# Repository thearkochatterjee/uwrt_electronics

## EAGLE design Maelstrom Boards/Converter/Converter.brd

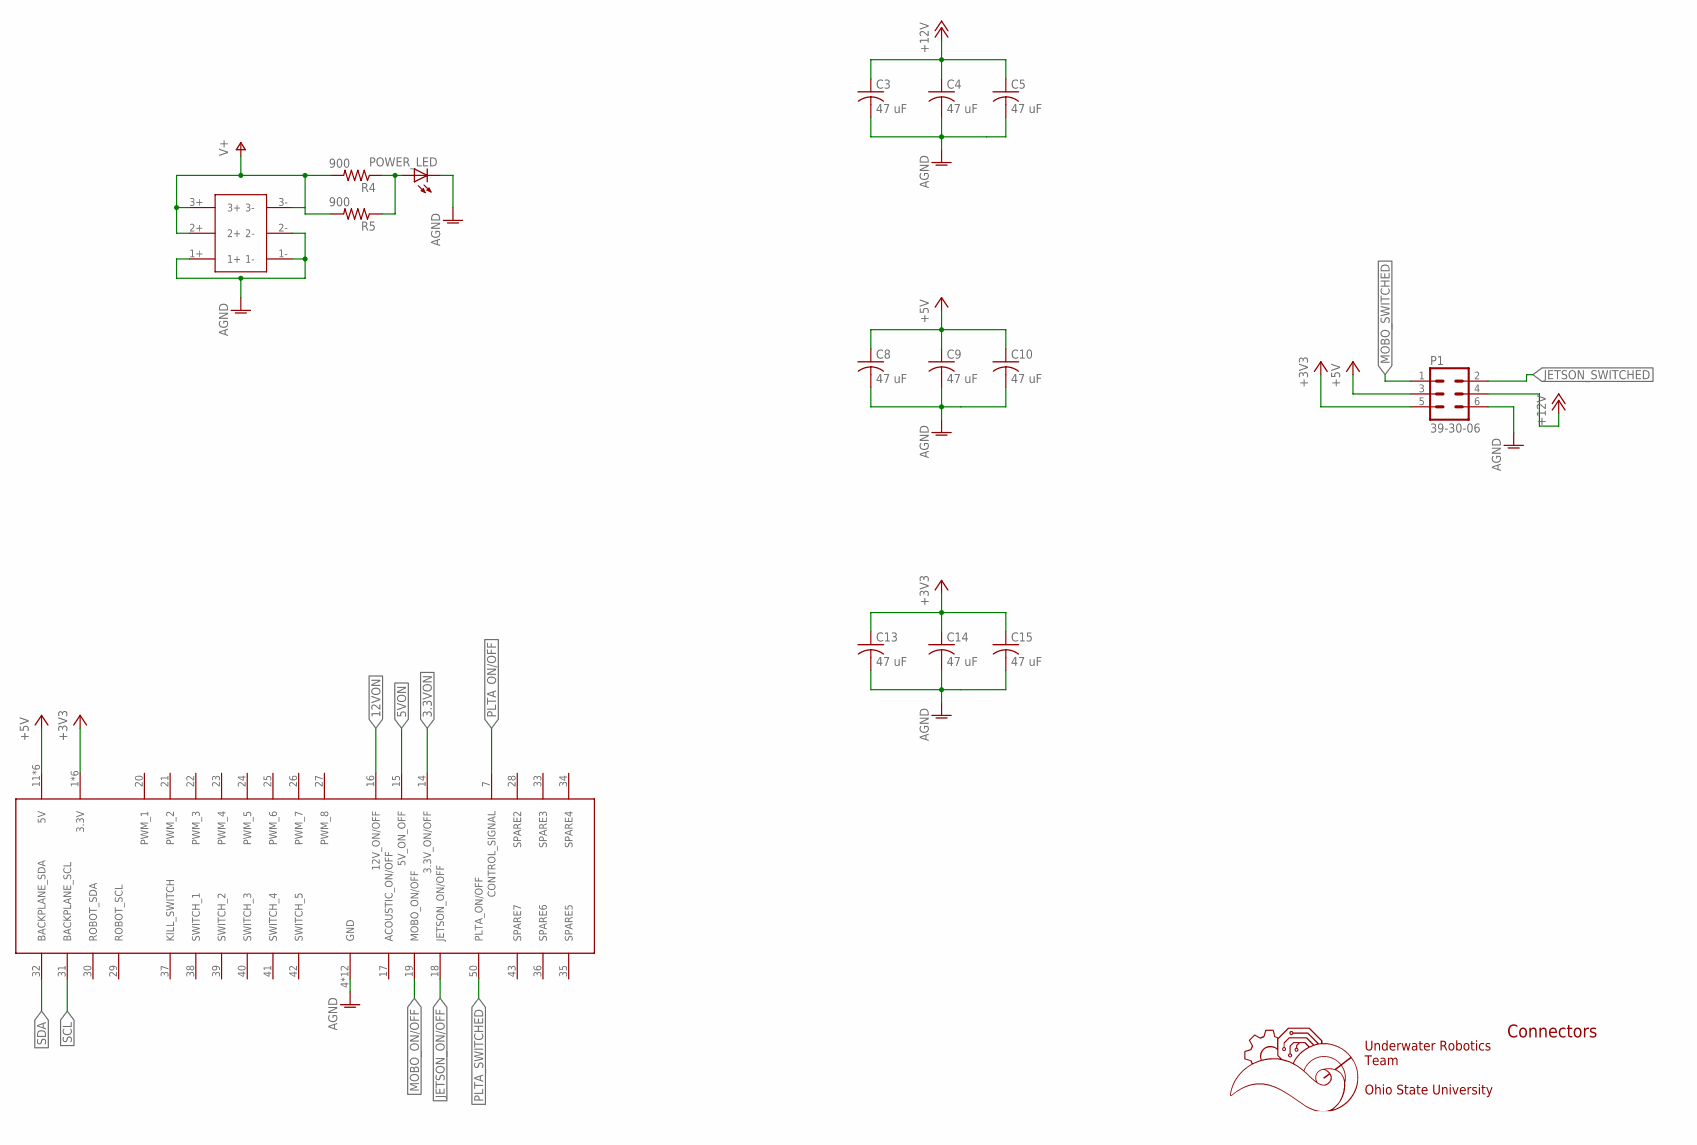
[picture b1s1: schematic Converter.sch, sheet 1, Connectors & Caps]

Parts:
C3, C4, C5, C8, C9, C10, C13, C14, C15: 47 uF; C1206K
P1: 39-30-06; 39-30-?06?
POWER_LED: LEDCHIPLED_0603; CHIPLED_0603
R4, R5: 900; R0603
U$1: 5530843-EDGE; 5530843-6-BOARDFINGERS
U$3: 6PIN-VERT; 6PIN_VERT

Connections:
3.3VON: U$1.14 (3.3V_ON/OFF); also elsewhere on the board
5VON: U$1.15 (5V_ON_OFF); also elsewhere on the board
12VON: U$1.16 (12V_ON/OFF); also elsewhere on the board
+3V3: C13.1, C14.1, C15.1, P1.5, U$1.1 (3.3V), U$1.2 (3.3V), U$1.3 (3.3V), U$1.54 (3.3V), U$1.55 (3.3V), U$1.56 (3.3V); also elsewhere on the board
+5V: C8.1, C9.1, C10.1, P1.3, U$1.11 (5V), U$1.12 (5V), U$1.13 (5V), U$1.44 (5V), U$1.45 (5V), U$1.46 (5V); also elsewhere on the board
+12V: C3.1, C4.1, C5.1, P1.4; also elsewhere on the board
AGND: C3.2, C4.2, C5.2, C8.2, C9.2, C10.2, C13.2, C14.2, C15.2, P1.6, POWER_LED.C, U$1.4 (GND), U$1.5 (GND), U$1.6 (GND), U$1.8 (GND), U$1.9 (GND), U$1.10 (GND), U$1.47 (GND), U$1.48 (GND), U$1.49 (GND), U$1.51 (GND), U$1.52 (GND), U$1.53 (GND), U$3.1+, U$3.1-, U$3.2-; also elsewhere on the board
JETSON_ON/OFF: U$1.18 (JETSON_ON/OFF); also elsewhere on the board
JETSON_SWITCHED: P1.2; also elsewhere on the board
MOBO_ON/OFF: U$1.19 (MOBO_ON/OFF); also elsewhere on the board
MOBO_SWITCHED: P1.1; also elsewhere on the board
unnamed: POWER_LED.A, R4.1, R5.1
PLTA_ON/OFF: U$1.7 (CONTROL_SIGNAL); also elsewhere on the board
PLTA_SWITCHED: U$1.50 (PLTA_ON/OFF); also elsewhere on the board
SCL: U$1.31 (BACKPLANE_SCL); also elsewhere on the board
SDA: U$1.32 (BACKPLANE_SDA); also elsewhere on the board
V+: R4.2, R5.2, U$3.2+, U$3.3+, U$3.3-; also elsewhere on the board

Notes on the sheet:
Underwater Robotics Team Ohio State University
Connectors

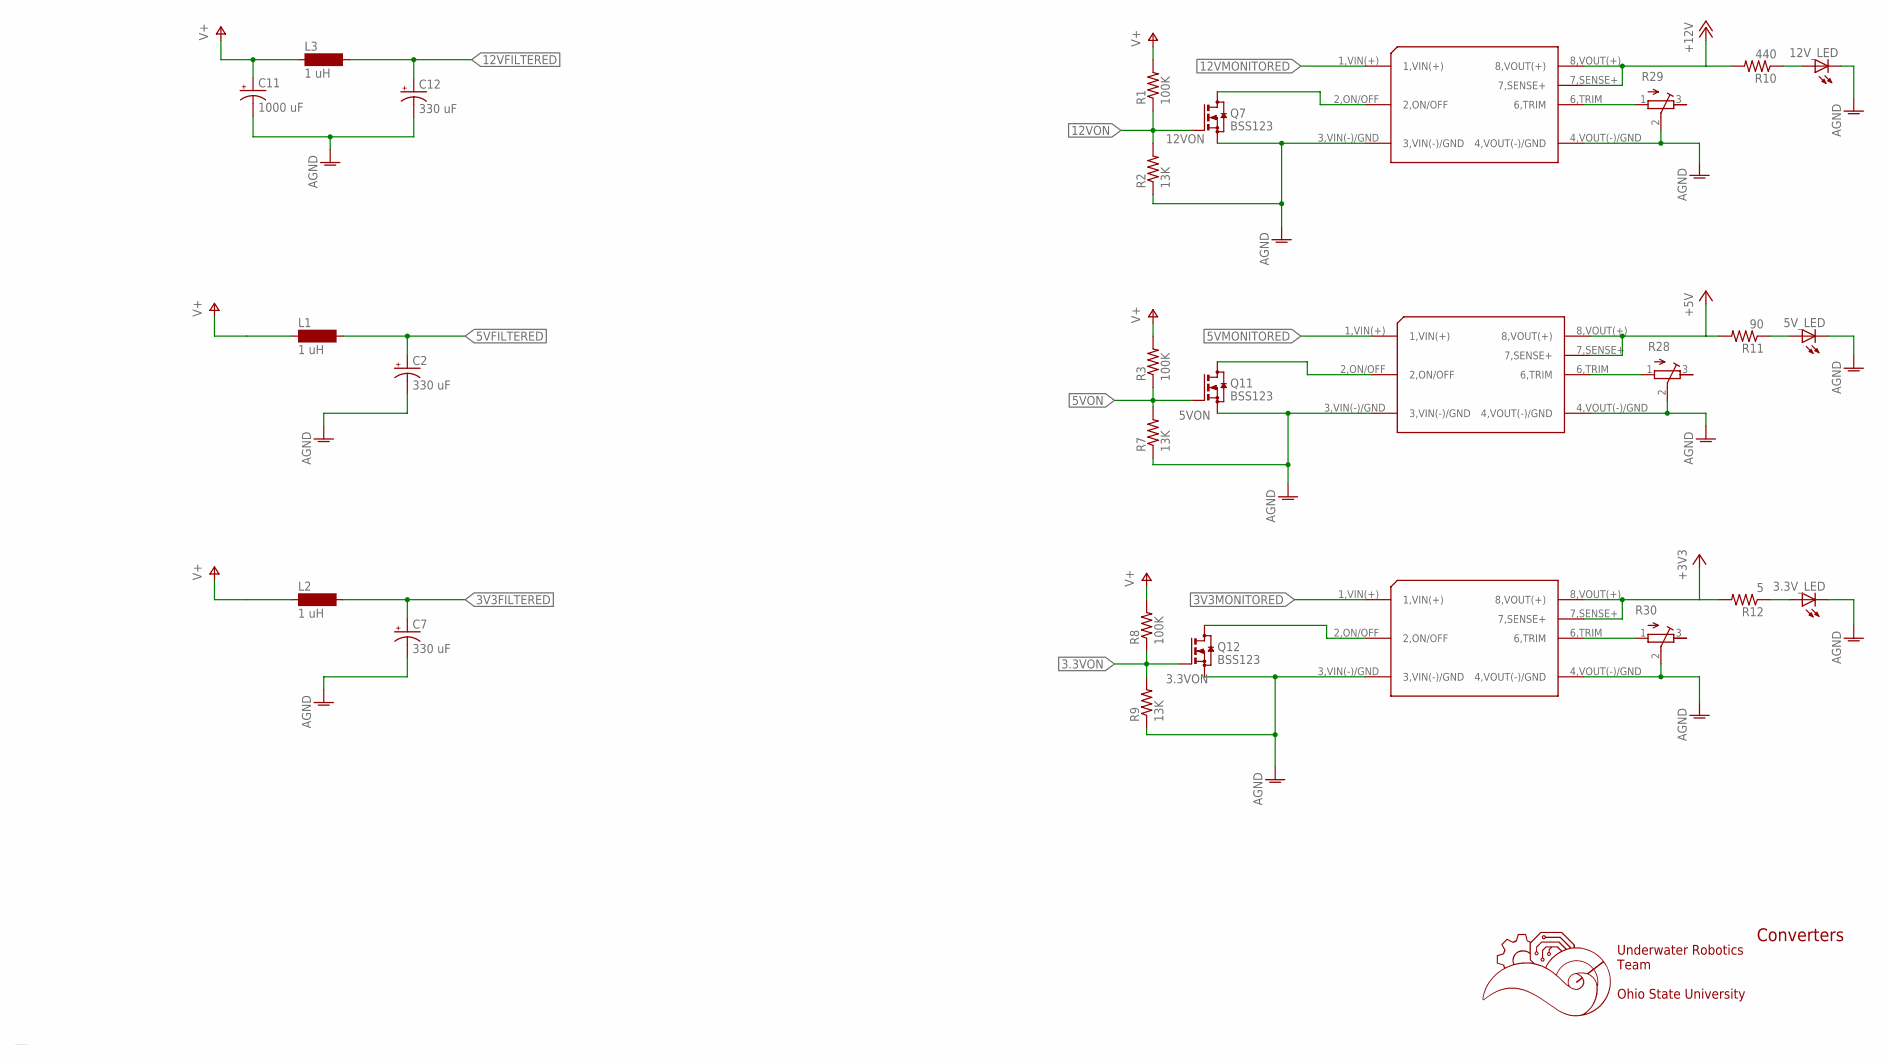
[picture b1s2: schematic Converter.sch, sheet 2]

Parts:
3.3VCONVERTER, 5VCONVERTER, 12VCONVERTER: CONVERTER
3.3V_LED, 5V_LED, 12V_LED: LEDCHIPLED_0603; CHIPLED_0603
C2, C7, C12: 330 uF; E5-10,5
C11: 1000 uF; E5-13
L1, L2, L3: 1 uH; MS85
Q7, Q11, Q12: BSS123; SOT23
R1, R3, R8: 100K; R0603
R2, R7, R9: 13K; R0603
R10: 440; R0603
R11: 90; R0603
R12: 5; R0603
R28, R29, R30: R-TRIMM3103; RTRIM3103

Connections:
3.3VON: Q12.1 (G), R8.1, R9.2; also elsewhere on the board
3V3FILTERED: C7.+, L2.2; also elsewhere on the board
3V3MONITORED: 3.3VCONVERTER.1,VIN(+); also elsewhere on the board
5VFILTERED: C2.+, L1.2; also elsewhere on the board
5VMONITORED: 5VCONVERTER.1,VIN(+); also elsewhere on the board
5VON: Q11.1 (G), R3.1, R7.2; also elsewhere on the board
12VFILTERED: C12.+, L3.2; also elsewhere on the board
12VMONITORED: 12VCONVERTER.1,VIN(+); also elsewhere on the board
12VON: Q7.1 (G), R1.1, R2.2; also elsewhere on the board
+3V3: 3.3VCONVERTER.7,SENSE+, 3.3VCONVERTER.8,VOUT(+), R12.2; also elsewhere on the board
+5V: 5VCONVERTER.7,SENSE+, 5VCONVERTER.8,VOUT(+), R11.2; also elsewhere on the board
+12V: 12VCONVERTER.7,SENSE+, 12VCONVERTER.8,VOUT(+), R10.2; also elsewhere on the board
AGND: 3.3VCONVERTER.3,VIN(-)/GND, 3.3VCONVERTER.4,VOUT(-)/GND, 3.3V_LED.C, 5VCONVERTER.3,VIN(-)/GND, 5VCONVERTER.4,VOUT(-)/GND, 5V_LED.C, 12VCONVERTER.3,VIN(-)/GND, 12VCONVERTER.4,VOUT(-)/GND, 12V_LED.C, C2.-, C7.-, C11.-, C12.-, Q7.2 (S), Q11.2 (S), Q12.2 (S), R2.1, R7.1, R9.1, R28.2 (S), R29.2 (S), R30.2 (S); also elsewhere on the board
unnamed: 12VCONVERTER.6,TRIM, R29.1 (A)
unnamed: 5VCONVERTER.6,TRIM, R28.1 (A)
unnamed: 3.3VCONVERTER.6,TRIM, R30.1 (A)
unnamed: 3.3VCONVERTER.2,ON/OFF, Q12.3 (D)
unnamed: 12V_LED.A, R10.1
unnamed: 5V_LED.A, R11.1
unnamed: 3.3V_LED.A, R12.1
unnamed: 12VCONVERTER.2,ON/OFF, Q7.3 (D)
unnamed: 5VCONVERTER.2,ON/OFF, Q11.3 (D)
V+: C11.+, L1.1, L2.1, L3.1, R1.2, R3.2, R8.2; also elsewhere on the board

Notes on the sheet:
C:/Users/blain/Downloads/Black and White.bmp
Underwater Robotics Team Ohio State University
Converters

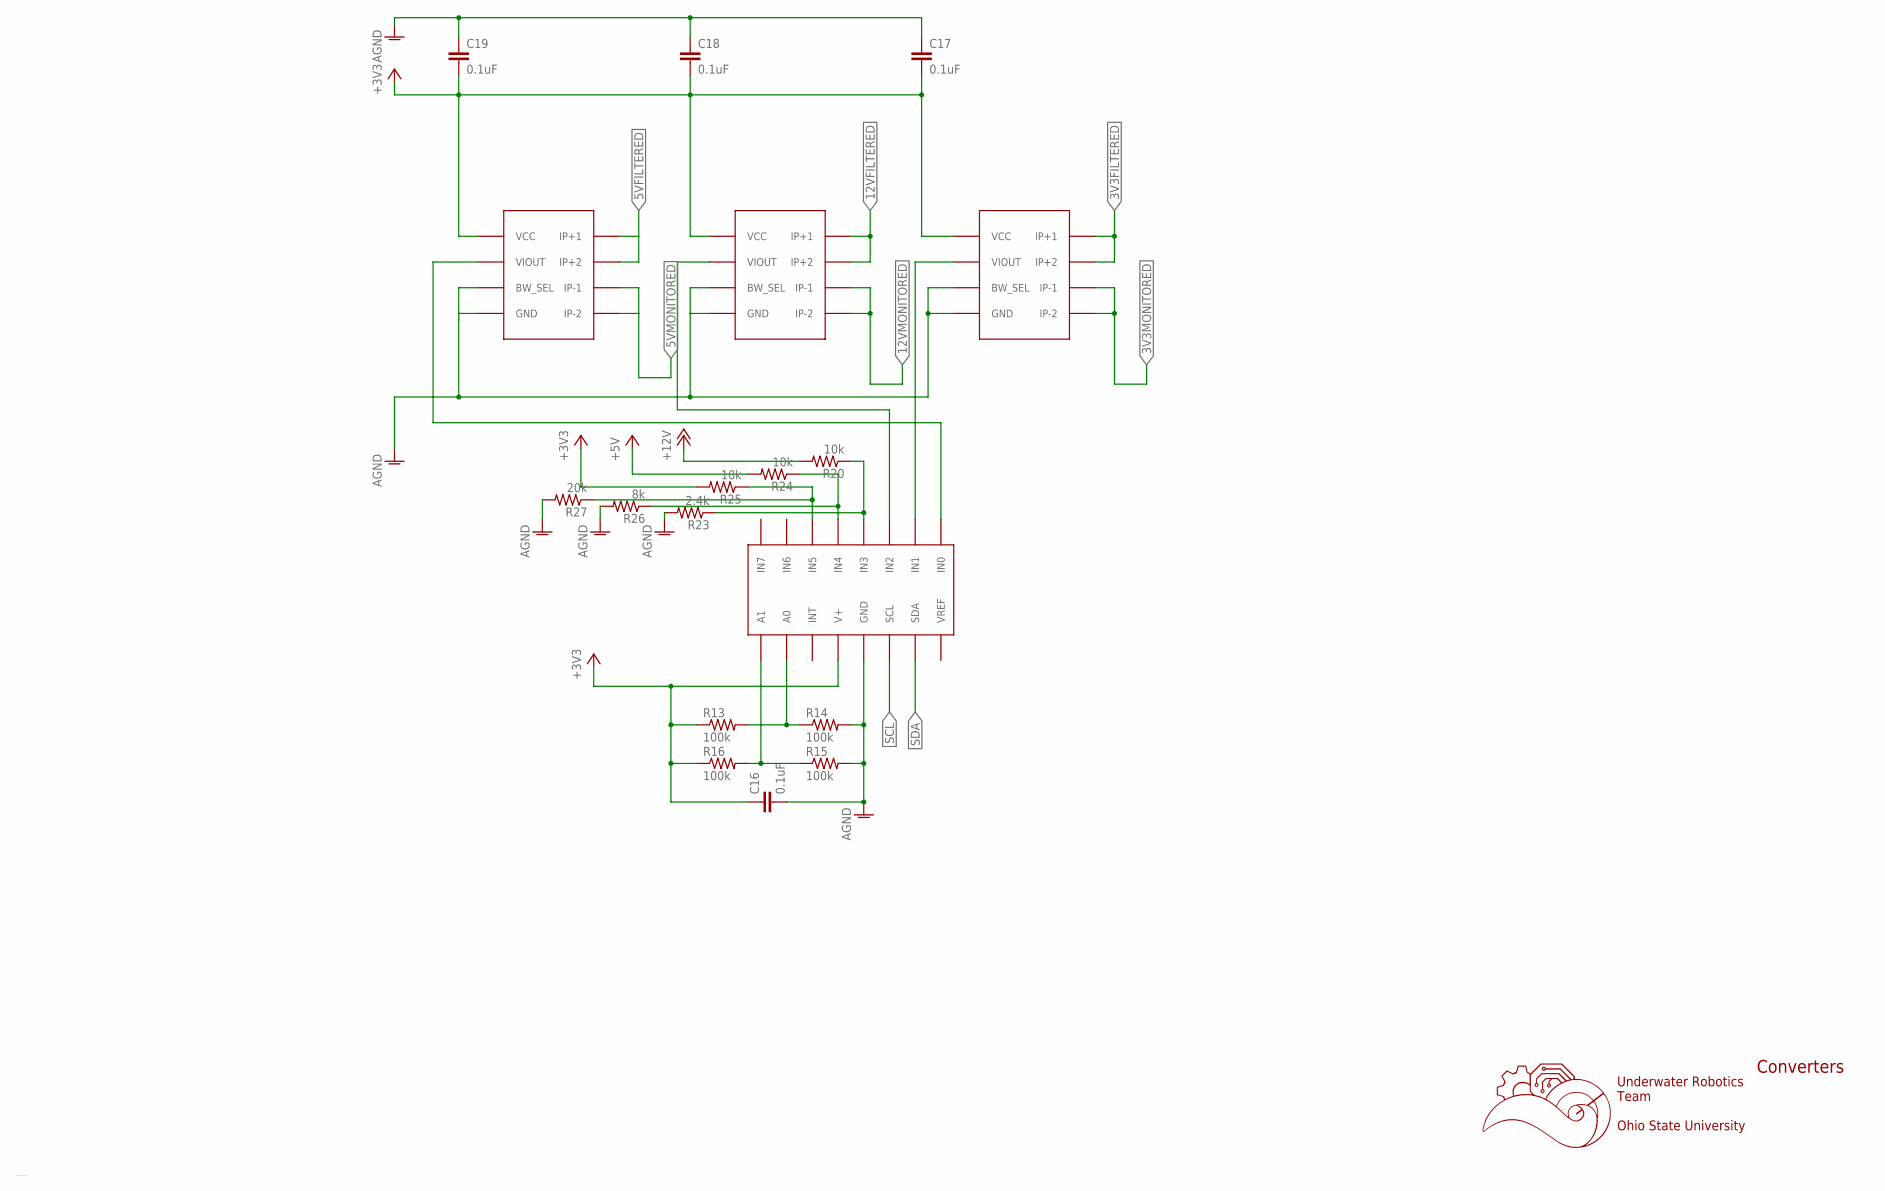
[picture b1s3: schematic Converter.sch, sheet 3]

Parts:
1C, 1C1, 1C2: ACS722; SOIC-8
C16, C17, C18, C19: 0.1uF; C0603
R13, R14, R15, R16: 100k; R0603
R20, R24, R25: 10k; R0603
R23: 2.4k; R0603
R26: 8k; R0603
R27: 20k; R0603
U$2: ADC128D818; TSSOP-16

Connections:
3V3FILTERED: 1C2.IP+1, 1C2.IP+2; also elsewhere on the board
3V3MONITORED: 1C2.IP-1, 1C2.IP-2; also elsewhere on the board
5VFILTERED: 1C.IP+1, 1C.IP+2; also elsewhere on the board
5VMONITORED: 1C.IP-1, 1C.IP-2; also elsewhere on the board
12VFILTERED: 1C1.IP+1, 1C1.IP+2; also elsewhere on the board
12VMONITORED: 1C1.IP-1, 1C1.IP-2; also elsewhere on the board
+3V3: 1C.VCC, 1C1.VCC, 1C2.VCC, C16.1, C17.2, C18.2, C19.2, R13.1, R16.1, R25.2, U$2.V+; also elsewhere on the board
+5V: R24.2; also elsewhere on the board
+12V: R20.2; also elsewhere on the board
AGND: 1C.BW_SEL, 1C.GND, 1C1.BW_SEL, 1C1.GND, 1C2.BW_SEL, 1C2.GND, C16.2, C17.1, C18.1, C19.1, R14.2, R15.2, R23.2, R26.2, R27.2, U$2.GND; also elsewhere on the board
unnamed: 1C.VIOUT, U$2.IN0
unnamed: 1C1.VIOUT, U$2.IN2
unnamed: 1C2.VIOUT, U$2.IN1
unnamed: R24.1, R26.1, U$2.IN4
unnamed: R25.1, R27.1, U$2.IN5
unnamed: R20.1, R23.1, U$2.IN3
unnamed: R13.2, R14.1, U$2.A0
unnamed: R15.1, R16.2, U$2.A1
SCL: U$2.SCL; also elsewhere on the board
SDA: U$2.SDA; also elsewhere on the board

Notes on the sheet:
C:/Users/blain/Downloads/Black and White.bmp
Underwater Robotics Team Ohio State University
Converters

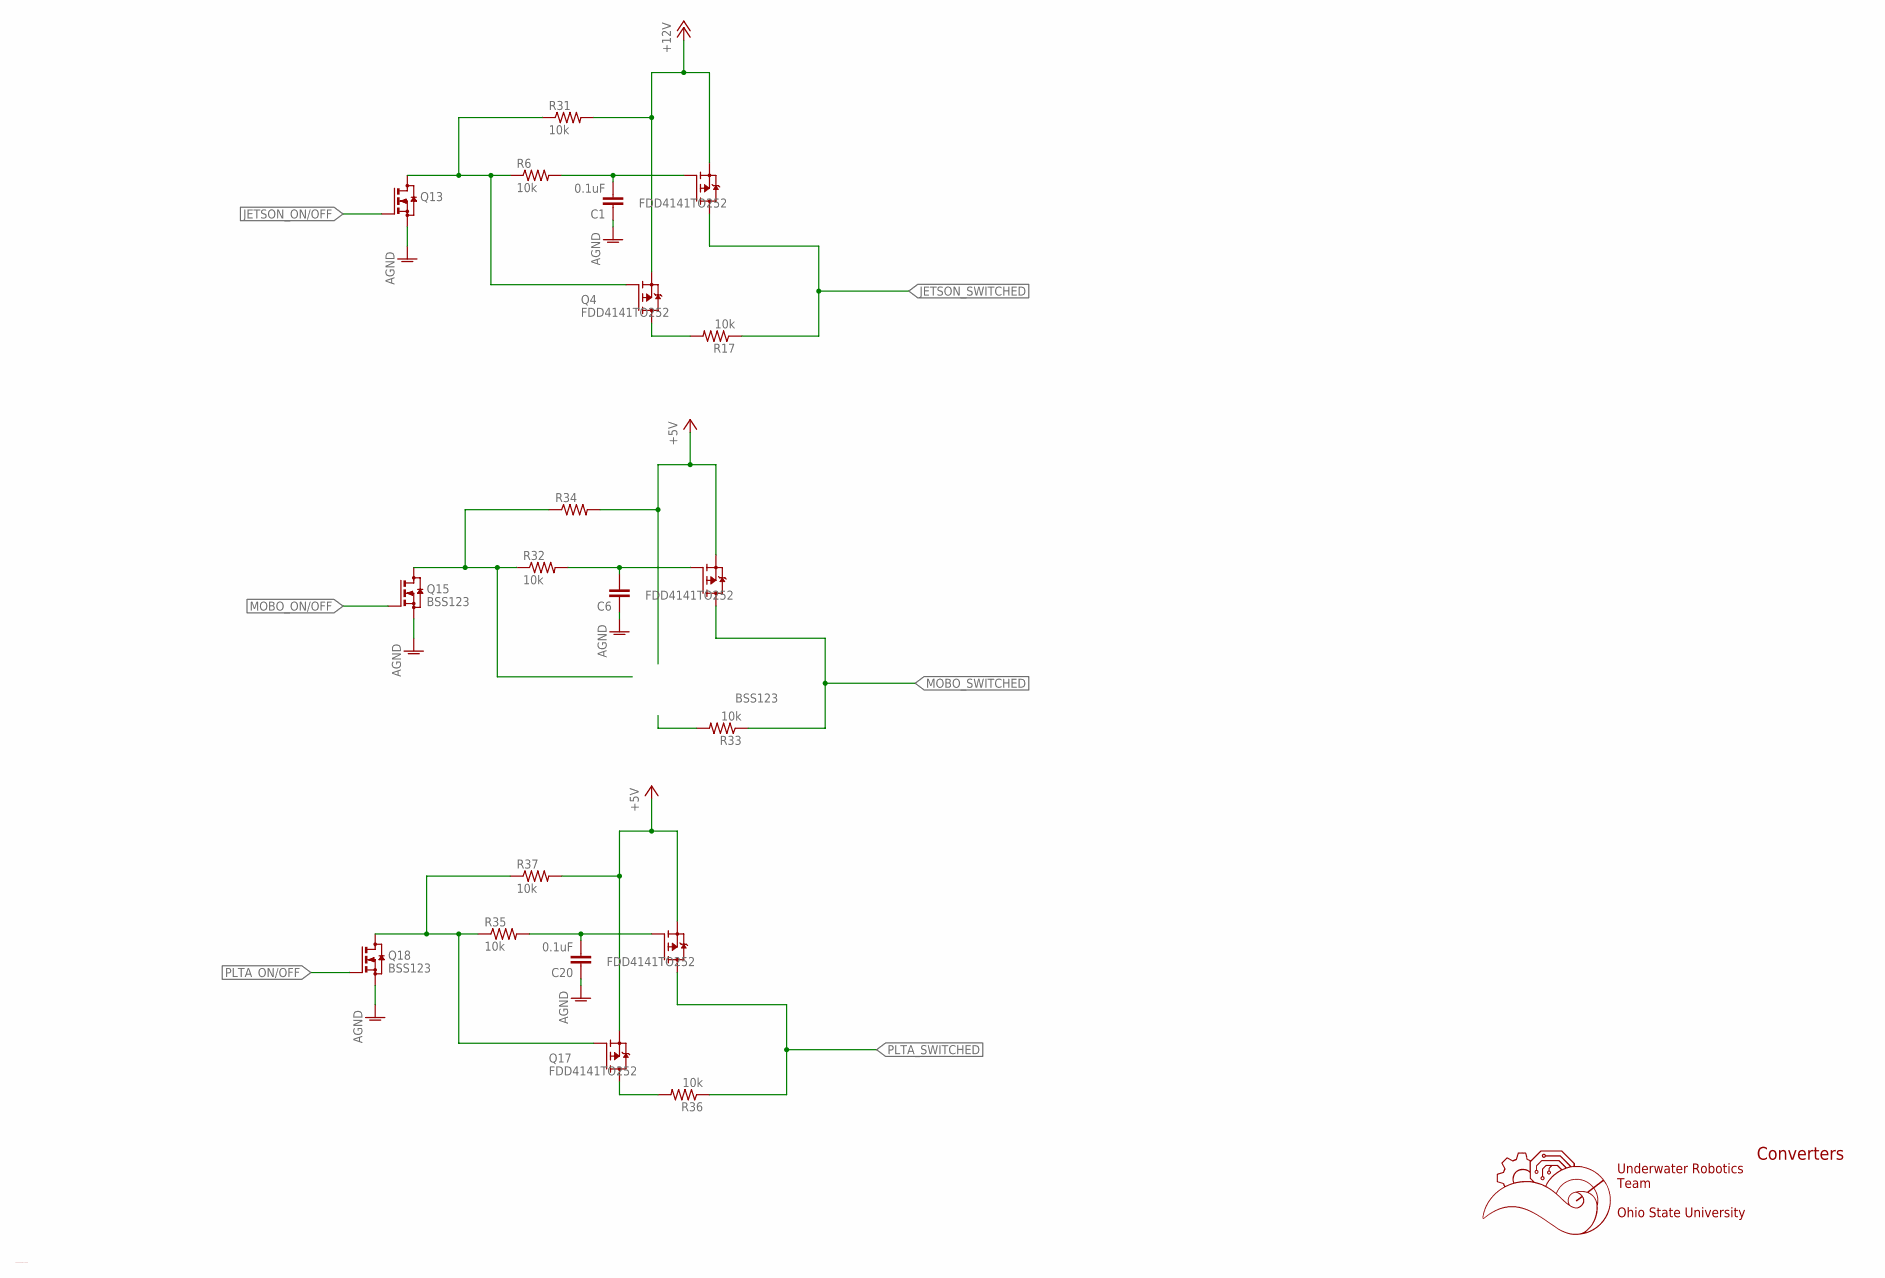
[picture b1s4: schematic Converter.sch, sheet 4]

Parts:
C1, C6, C20: 0.1uF; C0603
Q1, Q4, Q5, Q16, Q17: FDD4141TO252; TO252
Q13, Q15, Q18: BSS123; SOT23
R6, R17, R31, R32, R33, R34, R35, R36, R37: 10k; R0603

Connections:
+5V: Q5.2 (S), Q16.2 (S), Q17.2 (S), R34.2, R37.2; also elsewhere on the board
+12V: Q1.2 (S), Q4.2 (S), R31.2; also elsewhere on the board
AGND: C1.1, C6.1, C20.1, Q13.2 (S), Q15.2 (S), Q18.2 (S); also elsewhere on the board
JETSON_ON/OFF: Q13.1 (G); also elsewhere on the board
JETSON_SWITCHED: Q1.3 (D), R17.1; also elsewhere on the board
MOBO_ON/OFF: Q15.1 (G); also elsewhere on the board
MOBO_SWITCHED: Q5.3 (D), R33.1; also elsewhere on the board
unnamed: Q4.1 (G), Q13.3 (D), R6.1, R31.1
unnamed: Q4.3 (D), R17.2
unnamed: C1.2, Q1.1 (G), R6.2
unnamed: Q15.3 (D), R32.1, R34.1
unnamed: C6.2, Q5.1 (G), R32.2
unnamed: Q17.1 (G), Q18.3 (D), R35.1, R37.1
unnamed: C20.2, Q16.1 (G), R35.2
unnamed: Q17.3 (D), R36.2
PLTA_ON/OFF: Q18.1 (G); also elsewhere on the board
PLTA_SWITCHED: Q16.3 (D), R36.1; also elsewhere on the board

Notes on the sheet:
C:/Users/blain/Downloads/Black and White.bmp
Underwater Robotics Team Ohio State University
Converters

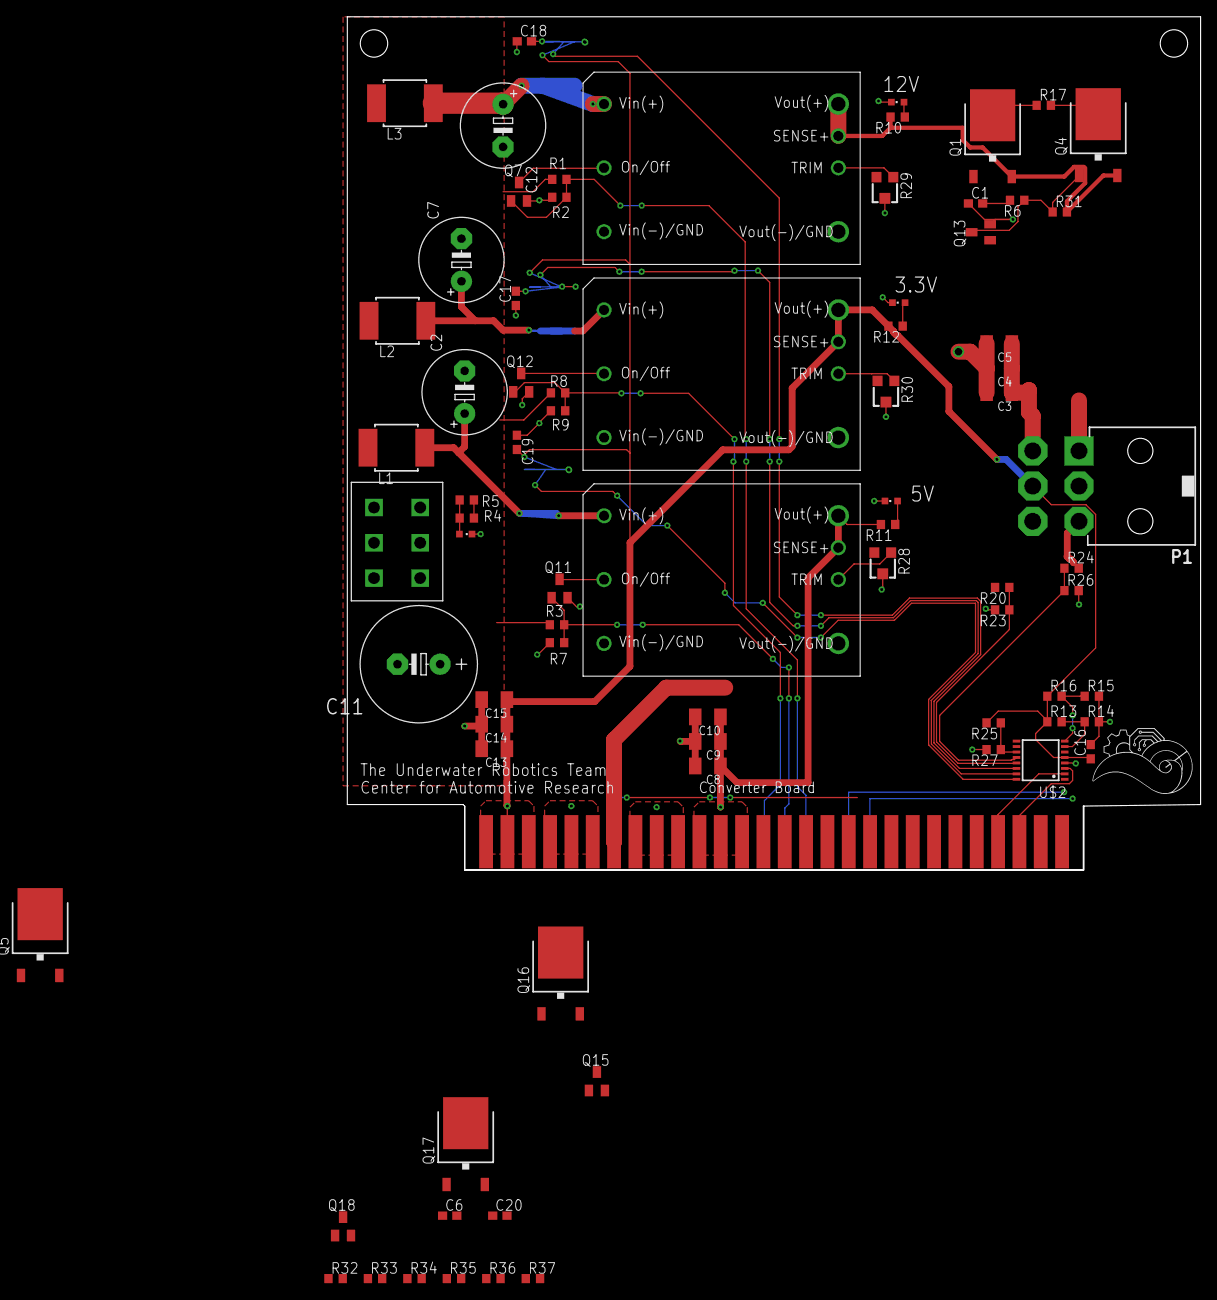
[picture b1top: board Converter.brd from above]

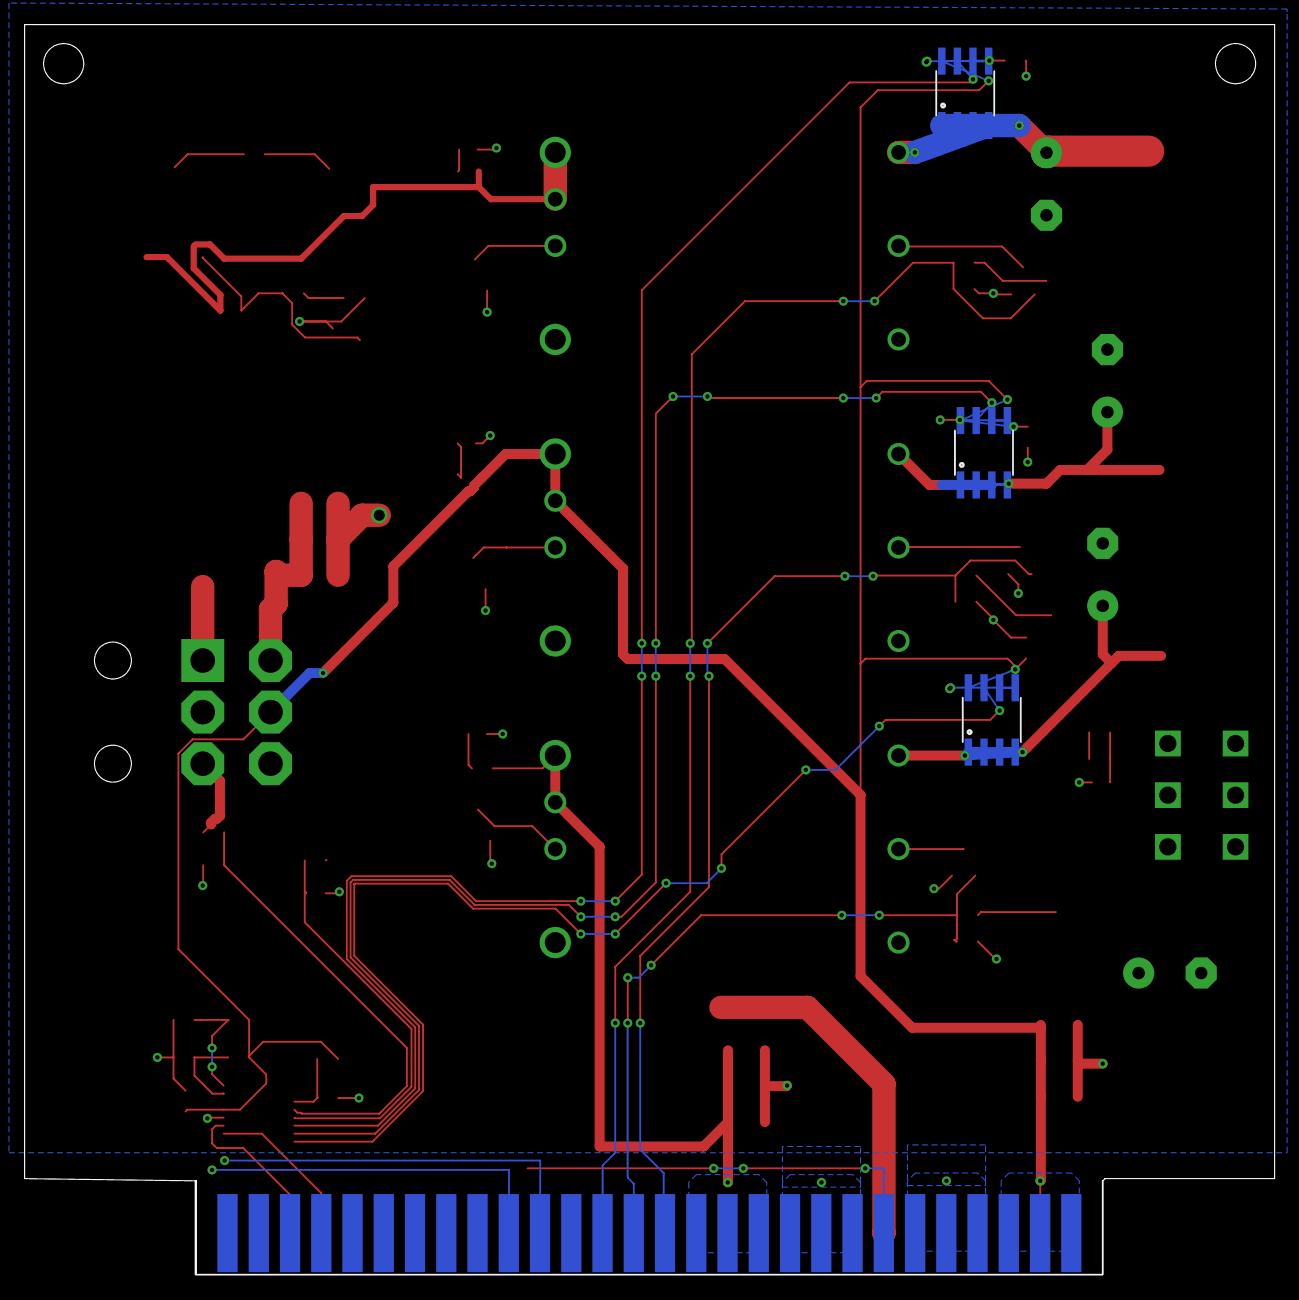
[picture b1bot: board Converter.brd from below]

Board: 2 copper layers, 101.6 x 101.6 mm, 81 parts (3 on the bottom side), 48 nets.

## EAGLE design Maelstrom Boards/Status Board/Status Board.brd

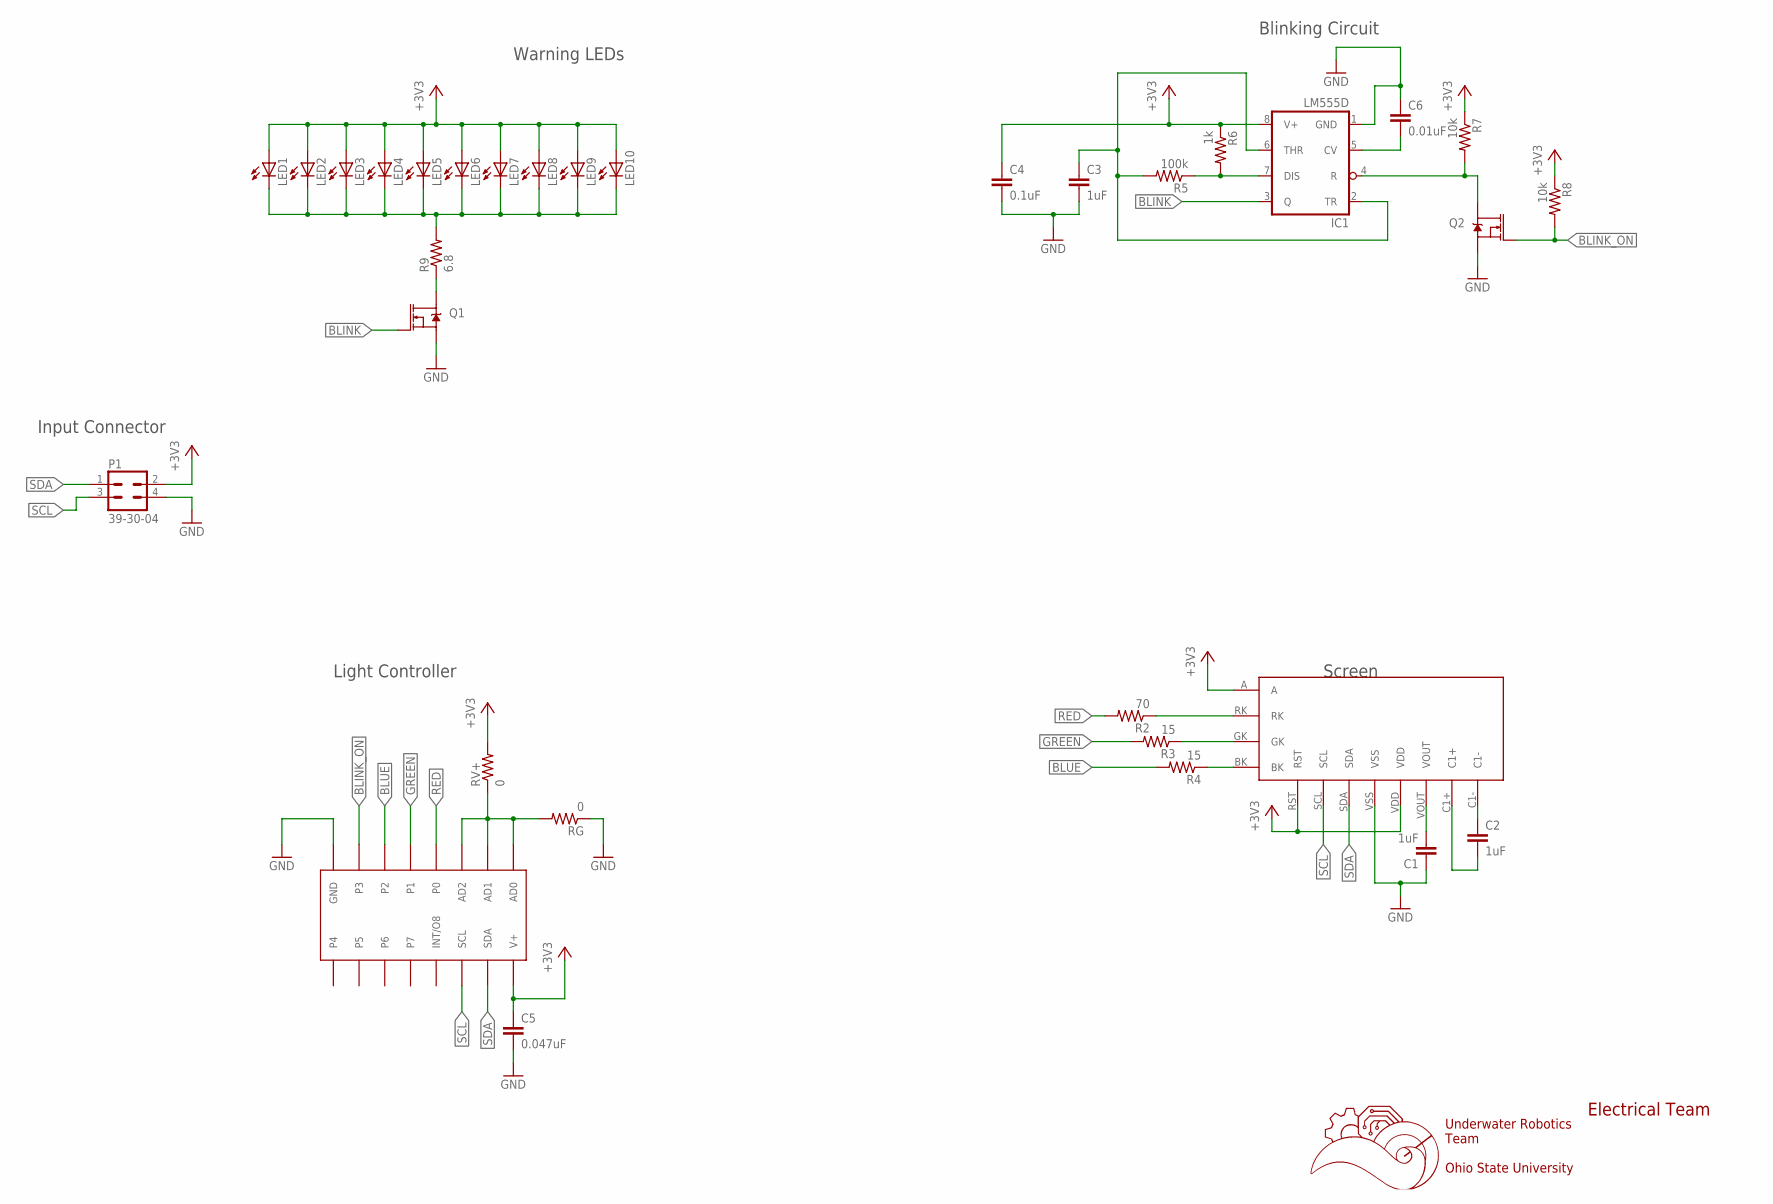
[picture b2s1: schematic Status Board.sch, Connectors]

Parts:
C1, C2, C3: 1uF; C0603
C4: 0.1uF; C0603
C5: 0.047uF; C0603
C6: 0.01uF; C0603
IC1: LM555D; SO08
LED1, LED2, LED3, LED4, LED5, LED6, LED7, LED8, LED9, LED10: LEDCHIPLED_0603; CHIPLED_0603
P1: 39-30-04; 39-30-?04?
Q1, Q2: 310mA/60V/1.6Ω; SOT323
R2: 70; R0603
R3, R4: 15; R0603
R5: 100k; R0603
R6: 1k; R0603
R7, R8: 10k; R0603
R9: 6.8; R0603
RG: 0; R0603
RV+: 0; R0603
U$1: NHD-C0220BIZ
U$2: MAX7315; TSSOP-16

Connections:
+3V3: C4.1, C5.1, IC1.8 (V+), LED1.A, LED2.A, LED3.A, LED4.A, LED5.A, LED6.A, LED7.A, LED8.A, LED9.A, LED10.A, P1.2, R6.1, R7.1, R8.1, RV+.2, U$1.A, U$1.RST, U$1.VDD, U$2.16 (V+)
BLINK: IC1.3 (Q), Q1.1 (G)
BLINK_OFF: IC1.4 (R), Q2.3 (D), R7.2
BLINK_ON: Q2.1 (G), R8.2, U$2.7 (P3)
BLUE: R4.2, U$2.6 (P2)
GND: C1.1, C3.2, C4.2, C5.2, C6.1, IC1.1 (GND), P1.4, Q1.2 (S), Q2.2 (S), RG.1, U$1.VSS, U$2.8 (GND)
GREEN: R3.2, U$2.5 (P1)
unnamed: R3.1, U$1.GK
unnamed: C2.1, U$1.C1-
unnamed: C1.2, U$1.VOUT
unnamed: C2.2, U$1.C1+
unnamed: R4.1, U$1.BK
unnamed: RG.2, RV+.1, U$2.1 (AD0), U$2.2 (AD1), U$2.3 (AD2)
unnamed: R2.1, U$1.RK
unnamed: C6.2, IC1.5 (CV)
unnamed: IC1.7 (DIS), R5.1, R6.2
unnamed: C3.1, IC1.2 (TR), IC1.6 (THR), R5.2
unnamed: Q1.3 (D), R9.1
unnamed: LED1.C, LED2.C, LED3.C, LED4.C, LED5.C, LED6.C, LED7.C, LED8.C, LED9.C, LED10.C, R9.2
RED: R2.2, U$2.4 (P0)
SCL: P1.3, U$1.SCL, U$2.14 (SCL)
SDA: P1.1, U$1.SDA, U$2.15 (SDA)

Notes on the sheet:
Underwater Robotics Team Ohio State University
Electrical Team
Warning LEDs
Blinking Circuit
Screen
Light Controller
Input Connector

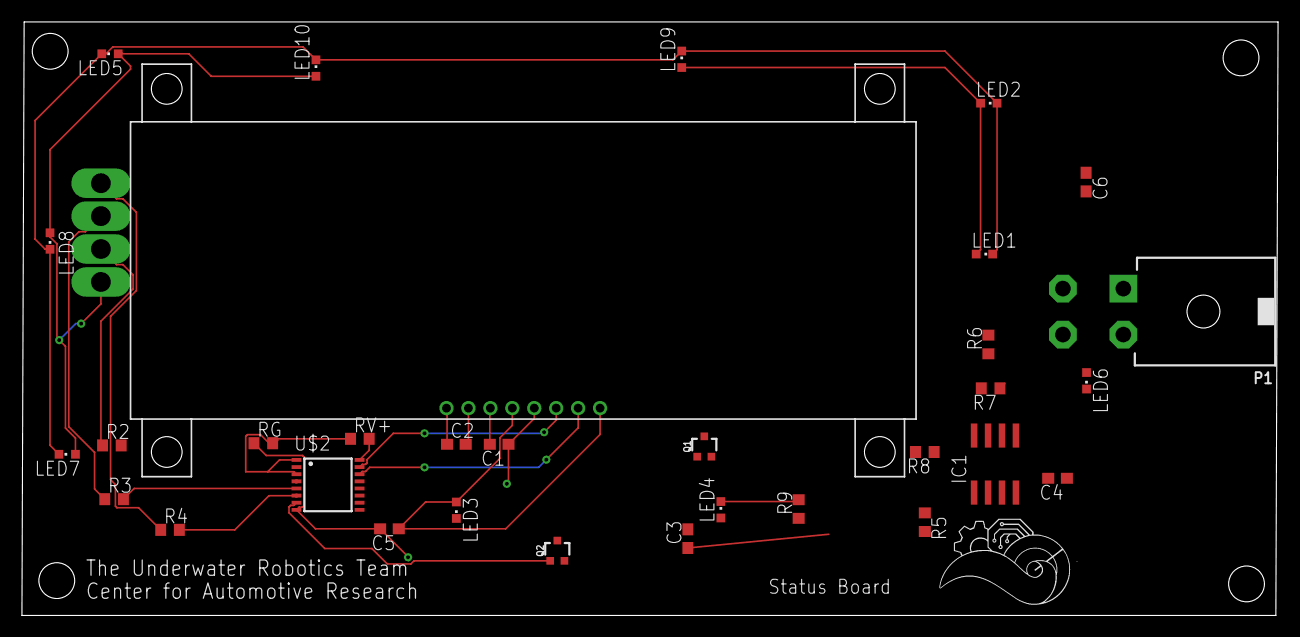
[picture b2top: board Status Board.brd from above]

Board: 2 copper layers, 114.5 x 54.1 mm, 32 parts (0 on the bottom side), 22 nets.

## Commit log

2019-04-14 Fixing Status Board
2019-05-19 Update Status Board
2019-05-19 Update Converter Board

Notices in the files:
parts and their libraries:
con-molex-mini-fit: Copyright (C) 2011, Bob Starr
SparkFun-DiscreteSemi: Licensing: Creative Commons ShareAlike 4.0 International - https://creativecommons.org/licenses/by-sa/4.0
